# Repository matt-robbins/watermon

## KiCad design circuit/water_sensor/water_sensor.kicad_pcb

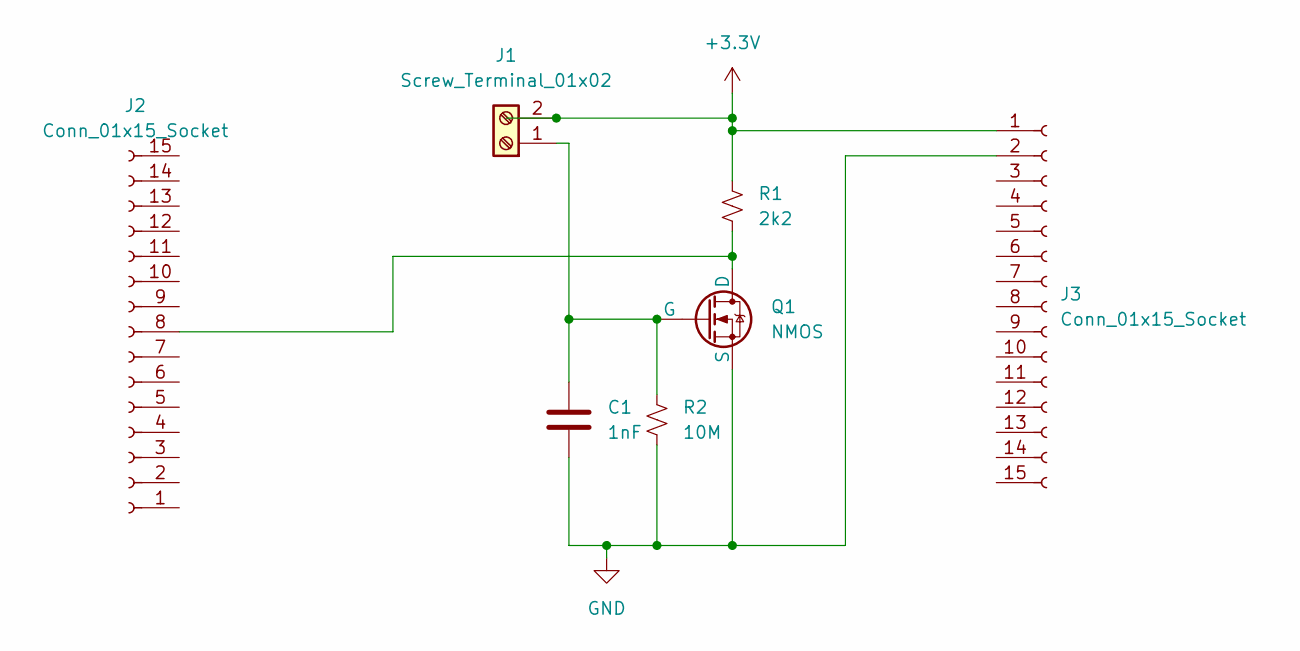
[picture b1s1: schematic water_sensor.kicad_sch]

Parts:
C1: 1nF; C_Disc_D4.7mm_W2.5mm_P5.00mm
J1: Screw_Terminal_01x02; TerminalBlock_Altech_AK300-2_P5.00mm
J2, J3: Conn_01x15_Socket; PinHeader_1x15_P2.54mm_Vertical
Q1: NMOS; TO-92L_Inline
R1: 2k2; R_Axial_DIN0207_L6.3mm_D2.5mm_P10.16mm_Horizontal
R2: 10M; R_Axial_DIN0207_L6.3mm_D2.5mm_P10.16mm_Horizontal

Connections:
+3.3V: J1.2, J3.1, R1.1
GND: C1.2, J3.2, Q1.3 (S), R2.2
unnamed: C1.1, J1.1, Q1.2 (G), R2.1
unnamed: J2.8, Q1.1 (D), R1.2

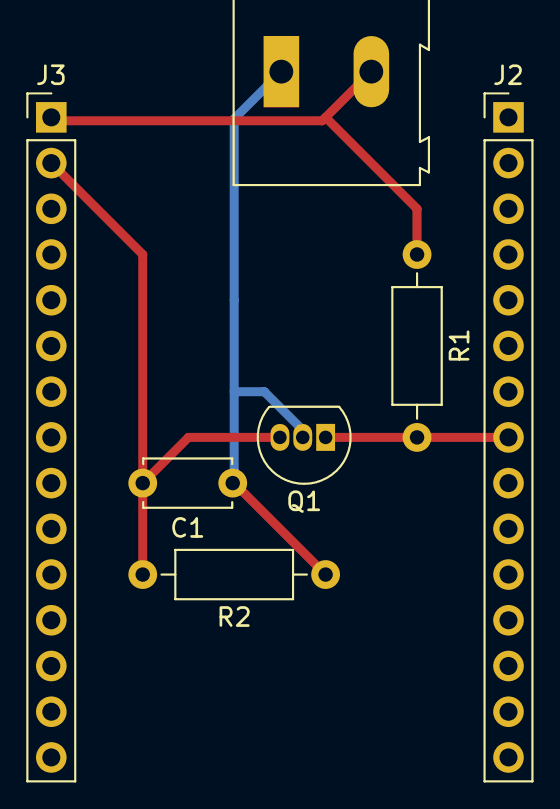
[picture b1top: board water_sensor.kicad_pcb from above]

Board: 2 copper layers, 7 parts (0 on the bottom side), 4 nets.

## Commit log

2024-01-17 watermon 1st commit
2024-01-17 mqtt integration
2024-01-18 secrets are in json files, simplified webpush code
2024-01-18 serve public vapid key via url
2024-01-18 added error checking to webpush, delete bad subscriptions
2024-01-18 added systemd service
2024-01-18 a few comments
2024-01-18 added esphome .yaml for esp32 devkit
2024-09-26 adapted to handle quad-plex pump system
2024-09-26 updated uc script
2024-09-30 changed manifest json and link in index.html to point to it.
2024-09-30 don't disable subscribe button
2024-09-30 added logging to webpush subscription
2024-09-30 poll for updates, in case message passing from web worker isn't working
2024-09-30 service worker pushes all messages
2024-09-30 send specific webpush messages
2024-09-30 UI reflects subscription status
2024-09-30 esp32 python has network list, and does some error checking etc. Probably not robust yet, but working on it.
2024-10-02 UC code, experimented with syntax, and rearranged
2024-10-03 broadcast channel opens on window load. Maybe this fixes iOS issue? Also, online indicator
2024-10-03 added port argument
2024-10-03 futzing with logging
2024-10-03 don't try to update non-existent indicator elements
2024-10-03 testpump topic if we set port
